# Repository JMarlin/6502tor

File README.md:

# 6502tor

This is the project page for the 6502tor project, a minimal educational computer designed to teach the fundamentals of how a computer actually operates near the lowest levels.

If you received an assembled rev1 board as a holiday gift, it probably looks something like this:

If you're interested in details about how the actual board is designed and built, you should check out the [hardware](hardware/README.md) section.

## Using The Hardware

This computer system is simultaneously incredibly simple while, by the token of complete open-endedness this implies, very complicated. With only a handful of controls, you can get the 6502tor to perform any function that can be done by *any other* computer.

For that reason, most of the system operation is going to be provided by a series of tutorial articles that will be published over time and which can be found below:

### Tutorials:
 - [0000 0001 - Overview and writing to memory](https://youtu.be/rqbeiZjz4c4)
 - [0000 0010 - Memory maps and binary](https://youtu.be/jSdUKUccR5Q)
 - [0000 0011 - Reset vector](https://youtu.be/KTeOp61t6co)
 - [0000 0100 - Executing your first instruction](https://youtu.be/9eZ2-8ygBwk)
 - [0000 0101 - Basic I/O](https://youtu.be/15wBBccO2ps)

### System Overview:

For the purpose of providing a quick reference so that you don't have to read through the articles if you need a reminder, the below chart provides a description of all the basic controls on the board:

1. **USB Port** - Provides power to the system and also, in more advanced uses, serial communication with a host machine

2. **User Register** - Provides 8 bits of output and can be written to at any address between `0x4000` and `0xBFFF`. The top two bits are also attached to the USB chip for more advanced serial I/O purposes:
   - Bit 6: RXD
   - Bit 7: CTS

3. **CPU Reset** - A toggle switch that causes the CPU to do an internal reset when pressed in and allows the CPU to begin executing from the reset vector stored in RAM at `0xFFFC` when released. 
Should be pressed in for at least 3 clock cycles whenever the clock source is changed or in any other scenario where you want the CPU to begin running from its default state.

4. **CLK LED** - Displays the clock signal being fed into the CPU.

5. **Write LED** - Displays whether the system is currently reading or writing data from/to the bus. Probably backwards from what you expect, *there is a write occurring when this LED is **OFF***

6. **Address LEDs** - Display the address that is currently being driven on the address bus, whether that's by the CPU or by the `address switches` (depending on the run/program mode)

7. **Data LEDs** - Display the data that is currently being driven on the data bus, whether that's by the CPU or by the `data switches` (depending on the run/program mode). Note that in run mode, the data bus is only driven during the *high* portion of the clock cycle.

8. **Slow Clock Speed Control** - When the clock source switch is set to 'slow', controls the speed of the slow CPU clock (clockwise is faster).

9. **Step Button** - When the clock source switch is set to 'manual', directly controls the CPU clock. When pressed in, sets the `CLK` signal to low and when not pressed in sets the `CLK` signal to high.
It should be noted that data only appears on the data bus during the high portion of the clock cycle.

10. **Clock Source Switch** - Switches the CPU between three different clock sources/speed ranges:

     - **Full** - Connects the CPU directly to the 5 megahertz crystal oscillator (the metal can in the middle of the board)

     - **Slow** - Connects the CPU to a much slower RC oscillator that can run the CPU between ~0.5 hertz and a few kilohertz depending on how the `Slow Clock Speed Control` is set

     - **Manual** - Connects the clock directly to a debounced pushbutton so that you can manually step through clock cycles as slowly as you would like

11. **Run/Program Switch** - Switches the board between `run` mode, in which the CPU is controlling everything, and the `program` mode in which the CPU is disconnected from the bus and the data switches, address switches, and deposit button can be used to manually place instructions and data into RAM.

12. **Deposit Button** - When the run/program switch is in program mode, depressing this button causes the value set on the data switches to be written to the location specified by the address switches. *This is a toggle button, so make sure to press it twice for each deposit*.

13. **Address Switches** - When the run/program switch is in program mode, the value of these switches is displayed on the address LEDs and the value stored at that location is displayed on the data LEDs. If the deposit switch is pressed, the value on the data switches is written to the address set on these switches.

14. **Data Switches** - When the run/program switch is in program mode, the value on these switches is written to the location set on the address switches. When the run/program switch is in the run mode, the value of the lowest five data switches can be read at addresses from `0x4000` to `0x8FFF`. In this mode, the top three bits connect to the USB chip as follows:

    - Bit 5: TXD
    - Bit 6: RTS
    - Bit 7: DTR 

### Memory Map:
| **Start** | **End** | **Description**                          |
|-----------|---------|------------------------------------------|
| 0x0000    | 0x3FFF  | 32K of RAM                               |
| 0x4000    | 0xBFFF  | Read data switches / Write user register |
| 0xC000    | 0xFFFF  | 32K of RAM                               |

## Reference Material And Resources
 - [6502 CPU datasheet](https://www.westerndesigncenter.com/wdc/documentation/w65c02s.pdf)
 - [6502 CPU instruction reference](https://www.masswerk.at/6502/6502_instruction_set.html)
 - [Online 6502 assembler](https://www.masswerk.at/6502/assembler.html) (for simple manual programming)
 - [cc65 compiler/cc65 assembler](https://github.com/cc65/cc65) (for more involved programming)
 - [RS232 serial communications on wikipedia](https://en.wikipedia.org/wiki/RS-232#Physical_interface)

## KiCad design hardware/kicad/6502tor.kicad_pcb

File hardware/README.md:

# Hardware

This directory contains the schematic and PCB project for the 6502tor hardware. The 6502tor board was designed in KiCAD, an EDA package that is free and open source. If you want to play with the CAD project, you can download KiCAD here:

 - [KiCAD Project Website](https://www.kicad.org/download/)

You can find the project in the `kicad` directory, but if you simply want to view the schematic you can find it in [the PDF in the same directory as this readme](6502tor_schematic.pdf)

## Caveats/Errata

Note that what is included here is the raw version of the project that was used to generate the first revision boards as shipped, and as such both include a handful of errors that are corrected on the shipped hardware with bodge wires:

 - Somehow KiCAD did not indicate to me that I managed to build two separate, unconnected ground nets. This can be fixed by making a connection between the ground pin (pin 10) on the user register IC (the 74574 next to the USB port) and the ground pin (pin 7) of any of the 7400 or 7404 chips in the glue logic section immediately below.

 - The order of the wires connecting the 74244 outputs back to the top three bits of the 74245 data tranceiver is reversed in the design from what it should be. This can be fixed by cutting the three traces that run just above the SMD capacitor located immediately to the left of the right-most 74245 (just above the DIP switches) and then connecting pins 2, 3, and 4 of that IC to pins 12, 14, and 16 of the adjacent 74244.

 - Bizarrely, there's absolutely no connection between the address bit 7 LED and its current-limiting resistor. The fix for this is to connect them.

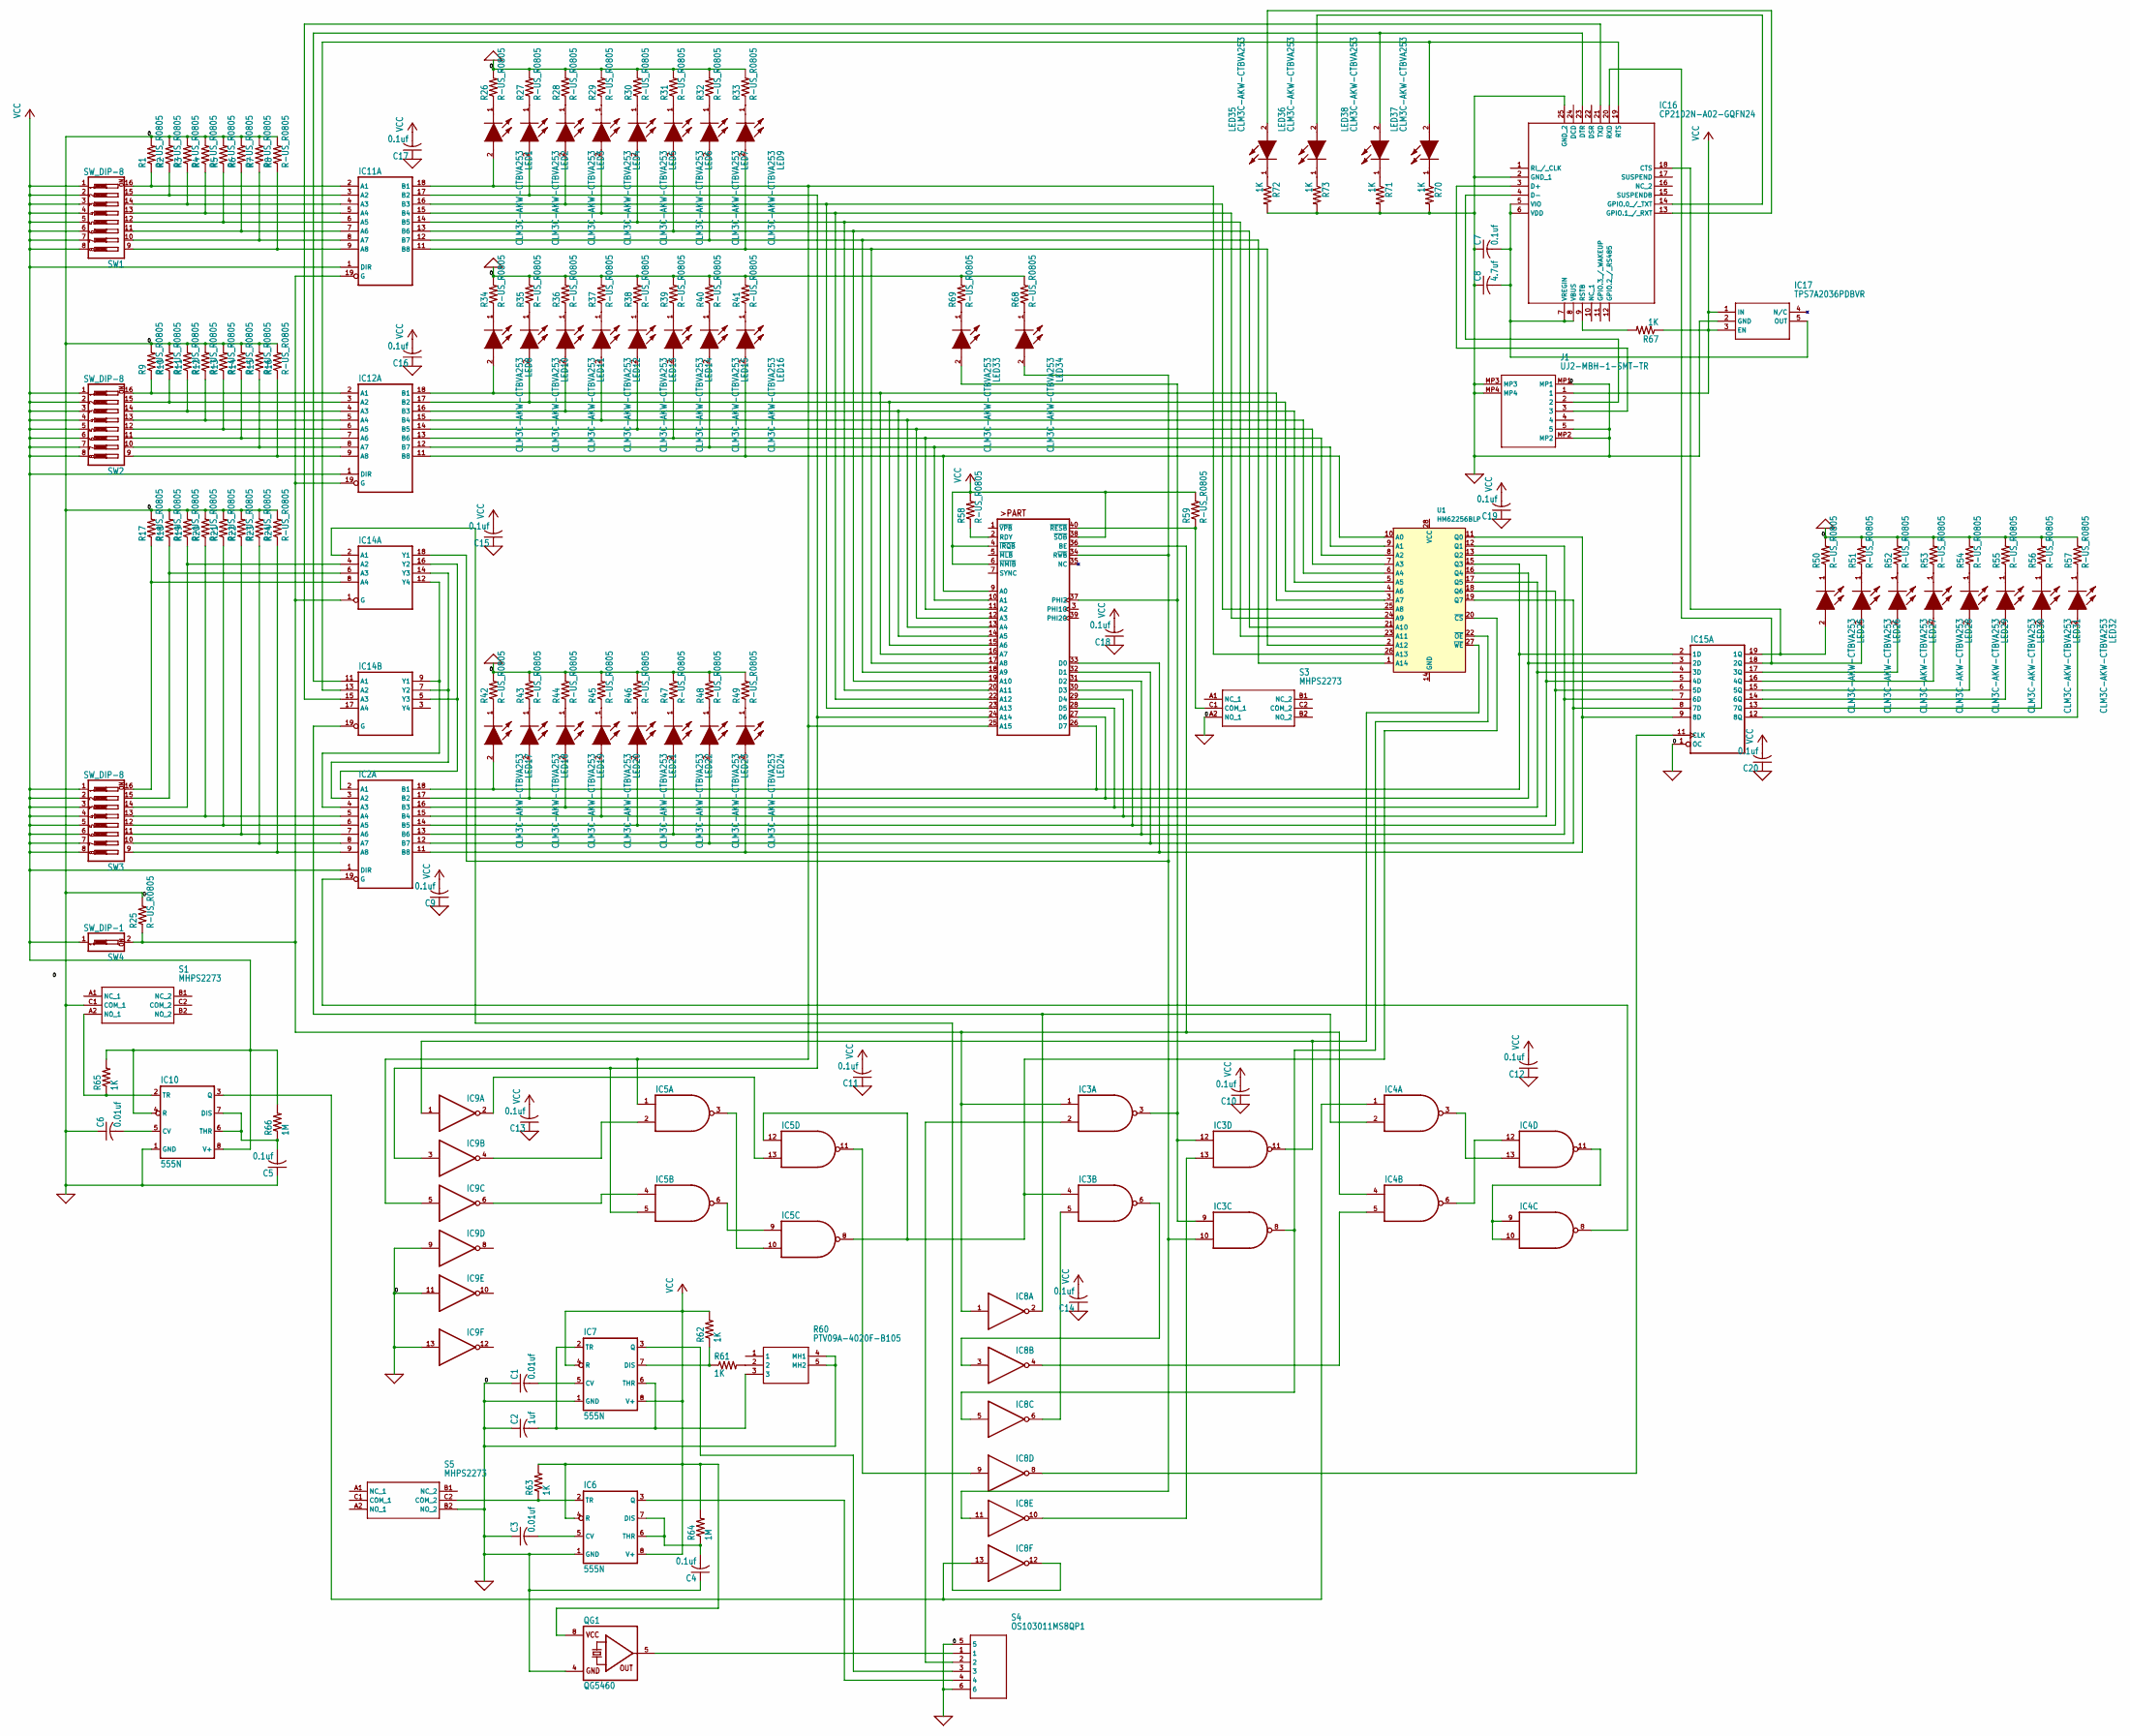
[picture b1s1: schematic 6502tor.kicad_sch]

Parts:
C1, C3, C6: 0.01uf; C1206
C2: 1uf; C1206
C4, C5, C7, C9, C10, C11, C12, C13, C14, C15, C16, C17, C18, C19, C20: 0.1uf; C1206
C8: 4.7uf; C1206
IC1: W65C02SP; DIL40
IC2, IC11, IC12: 74245N; DIL20
IC3, IC4, IC5: 7400N; DIL14
IC6, IC7, IC10: 555N; DIL08
IC8, IC9: 7404N; DIL14
IC14: 74244N; DIL20
IC15: 74574N; DIL20
IC16: CP2102N-A02-GQFN24; QFN50P400X400X80-25N
IC17: TPS7A2036PDBVR; SOT95P280X145-5N
J1: UJ2-MBH-1-SMT-TR; UJ2MBH1SMTTR
LED1, LED2, LED3, LED4, LED5, LED6, LED7, LED8, LED9, LED10, LED11, LED12, LED13, LED14, LED15, LED16, LED17, LED18, LED19, LED20, LED21, LED22, LED23, LED24, LED25, LED26, LED27, LED28, LED29, LED30, LED31, LED32, LED33, LED34, LED35, LED36, LED37, LED38: CLM3C-AKW-CTBVA253; LEDM3020X140N
QG1: QG5460; DIL08S
R1, R2, R3, R4, R5, R6, R7, R8, R9, R10, R11, R12, R13, R14, R15, R16, R17, R18, R19, R20, R21, R22, R23, R24, R25, R26, R27, R28, R29, R30, R31, R32, R33, R34, R35, R36, R37, R38, R39, R40, R41, R42, R43, R44, R45, R46, R47, R48, R49, R50, R51, R52, R53, R54, R55, R56, R57, R58, R59, R68, R69: R-US_R0805; R0805
R60: PTV09A-4020F-B105; PTV09A4020FB103
R61, R62, R63, R65, R67, R70, R71, R72, R73: 1K; R0805
R64, R66: 1M; R0805
S1, S3, S5: MHPS2273
S4: OS103011MS8QP1
SW1, SW2, SW3: SW_DIP-8; EDG-08
SW4: SW_DIP-1; EDG-01
U1: HM62256BLP; DIP-28_W15.24mm

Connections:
0: C1.1, C2.1, C3.1, C4.1, C5.1, C6.1, C7.1, C8.1, C9.1, C10.1, C11.1, C12.1, C13.1, C14.1, C15.1, C16.1, C17.1, C18.1, C19.1, C20.1, IC1.21 (VSS), IC2.10 (GND), IC3.7 (GND), IC4.7 (GND), IC5.7 (GND), IC6.1 (GND), IC7.1 (GND), IC8.7 (GND), IC9.7 (GND), IC9.9 (I), IC9.11 (I), IC9.13 (I), IC10.1 (GND), IC11.10 (GND), IC12.10 (GND), IC14.10 (GND), IC15.1 (OC), IC15.10 (GND), IC16.2 (GND_1), IC16.25 (GND_2), IC17.2 (GND), J1.5, J1.MP1, J1.MP2, J1.MP3, J1.MP4, QG1.4 (GND), R1.2, R2.2, R3.2, R4.2, R5.2, R6.2, R7.2, R8.2, R9.2, R10.2, R11.2, R12.2, R13.2, R14.2, R15.2, R16.2, R17.2, R18.2, R19.2, R20.2, R21.2, R22.2, R23.2, R24.2, R25.2, R26.2, R27.2, R28.2, R29.2, R30.2, R31.2, R32.2, R33.2, R34.2, R35.2, R36.2, R37.2, R38.2, R39.2, R40.2, R41.2, R42.2, R43.2, R44.2, R45.2, R46.2, R47.2, R48.2, R49.2, R50.2, R51.2, R52.2, R53.2, R54.2, R55.2, R56.2, R57.2, R60.4 (MH1), R60.5 (MH2), R68.2, R69.2, R70.2, R71.2, R72.2, R73.2, S1.C1 (COM_1), S3.A2 (NO_1), S4.5, S4.6, S5.B2 (NO_2), U1.14 (GND)
unnamed: C1.2, IC7.5 (CV)
unnamed: C2.2, IC7.2 (TR), IC7.6 (THR), R60.3
unnamed: C3.2, IC6.5 (CV)
unnamed: C4.2, IC6.6 (THR), IC6.7 (DIS), R64.1
unnamed: C5.2, IC10.6 (THR), IC10.7 (DIS), R66.1
unnamed: C6.2, IC10.5 (CV)
unnamed: C7.2, C8.2, IC16.5 (VIO), IC16.6 (VDD), IC16.7 (VREGIN), IC16.8 (VBUS), IC17.5 (OUT)
unnamed: IC1.2 (RDY), R58.1
unnamed: IC1.9 (A0), IC12.11 (B8), LED16.2 (A), U1.10 (A0)
unnamed: IC1.10 (A1), IC12.12 (B7), LED15.2 (A), U1.9 (A1)
unnamed: IC1.11 (A2), IC12.13 (B6), LED14.2 (A), U1.8 (A2)
unnamed: IC1.12 (A3), IC12.14 (B5), LED13.2 (A), U1.7 (A3)
unnamed: IC1.13 (A4), IC12.15 (B4), LED12.2 (A), U1.6 (A4)
unnamed: IC1.14 (A5), IC12.16 (B3), LED11.2 (A), U1.5 (A5)
unnamed: IC1.15 (A6), IC12.17 (B2), LED10.2 (A), U1.4 (A6)
unnamed: IC1.16 (A7), IC12.18 (B1), LED8.2 (A), U1.3 (A7)
unnamed: IC1.17 (A8), IC11.11 (B8), LED9.2 (A), U1.2 (A12)
unnamed: IC1.18 (A9), IC11.12 (B7), LED7.2 (A), U1.1 (A14)
unnamed: IC1.19 (A10), IC11.13 (B6), LED6.2 (A), U1.21 (A10)
unnamed: IC1.20 (A11), IC11.14 (B5), LED5.2 (A), U1.23 (A11)
unnamed: IC1.22 (A12), IC11.15 (B4), LED4.2 (A), U1.24 (A9)
unnamed: IC1.23 (A13), IC11.16 (B3), LED3.2 (A), U1.25 (A8)
unnamed: IC1.24 (A14), IC5.5 (I1), IC9.3 (I), IC11.17 (B2), LED2.2 (A)
unnamed: IC1.25 (A15), IC5.1 (I0), IC9.5 (I), IC11.18 (B1), LED1.2 (A), U1.26 (A13)
unnamed: IC1.26 (D7), IC2.18 (B1), IC15.2 (1D), LED17.2 (A), U1.15 (Q3)
unnamed: IC1.27 (D6), IC2.17 (B2), IC15.3 (2D), LED18.2 (A), U1.16 (Q4)
unnamed: IC1.28 (D5), IC2.16 (B3), IC15.4 (3D), LED19.2 (A), U1.17 (Q5)
unnamed: IC1.29 (D4), IC2.15 (B4), IC15.5 (4D), LED20.2 (A), U1.13 (Q2)
unnamed: IC1.30 (D3), IC2.14 (B5), IC15.6 (5D), LED21.2 (A), U1.18 (Q6)
unnamed: IC1.31 (D2), IC2.13 (B6), IC15.7 (6D), LED22.2 (A), U1.12 (Q1)
unnamed: IC1.32 (D1), IC2.12 (B7), IC15.8 (7D), LED23.2 (A), U1.19 (Q7)
unnamed: IC1.33 (D0), IC2.11 (B8), IC15.9 (8D), LED24.2 (A), U1.11 (Q0)
unnamed: IC1.34 (R~WB), IC3.10 (I1), IC8.11 (I), IC14.18 (Y1), LED34.2 (A)
unnamed: IC1.36 (BE), IC3.1 (I0), IC4.4 (I0), IC8.1 (I), IC11.19 (G), IC12.19 (G), IC14.1 (G), R25.1, SW4.2
unnamed: IC1.37 (PHI2), IC3.3 (O), IC3.9 (I0), IC3.12 (I0), LED33.2 (A)
unnamed: IC1.40 (~RESB), R59.1, S3.C1 (COM_1)
unnamed: IC3.2 (I1), S4.2
unnamed: IC3.4 (I0), IC5.8 (O), IC5.12 (I0), U1.20 (~CS)
unnamed: IC3.5 (I1), IC8.6 (O)
unnamed: IC3.6 (O), IC8.3 (I)
unnamed: IC3.8 (O), IC8.5 (I), U1.22 (~OE)
unnamed: IC3.11 (O), IC9.1 (I), U1.27 (~WE)
unnamed: IC3.13 (I1), IC8.10 (O)
unnamed: IC4.5 (I1), IC8.4 (O)
unnamed: IC2.19 (G), IC4.8 (O)
unnamed: IC4.9 (I0), IC4.10 (I1), IC4.11 (O)
unnamed: IC4.6 (O), IC4.12 (I0)
unnamed: IC4.3 (O), IC4.13 (I1)
unnamed: IC5.2 (I1), IC9.4 (O)
unnamed: IC5.4 (I0), IC9.6 (O)
unnamed: IC5.6 (O), IC5.9 (I0)
unnamed: IC5.3 (O), IC5.10 (I1)
unnamed: IC5.11 (O), IC8.9 (I)
unnamed: IC5.13 (I1), IC9.2 (O)
unnamed: IC6.2 (TR), R63.1, S5.C2 (COM_2)
unnamed: IC6.3 (Q), S4.4
unnamed: IC7.3 (Q), S4.3
unnamed: IC7.7 (DIS), R61.1, R62.1
unnamed: IC10.2 (TR), R65.1, S1.A2 (NO_1)
unnamed: IC4.1 (I0), IC8.13 (I), IC10.3 (Q)
unnamed: IC11.2 (A1), R1.1, SW1.16
unnamed: IC11.3 (A2), R2.1, SW1.15
unnamed: IC11.4 (A3), R3.1, SW1.14
unnamed: IC11.5 (A4), R4.1, SW1.13
unnamed: IC11.6 (A5), R5.1, SW1.12
unnamed: IC11.7 (A6), R6.1, SW1.11
unnamed: IC11.8 (A7), R7.1, SW1.10
unnamed: IC11.9 (A8), R8.1, SW1.9
unnamed: IC12.2 (A1), R9.1, SW2.16
unnamed: IC12.3 (A2), R10.1, SW2.15
unnamed: IC12.4 (A3), R11.1, SW2.14
unnamed: IC12.5 (A4), R12.1, SW2.13
unnamed: IC12.6 (A5), R13.1, SW2.12
unnamed: IC12.7 (A6), R14.1, SW2.11
unnamed: IC12.8 (A7), R15.1, SW2.10
unnamed: IC12.9 (A8), R16.1, SW2.9
unnamed: IC8.12 (O), IC14.2 (A1)
unnamed: IC14.4 (A2), R19.1, SW3.14
unnamed: IC14.6 (A3), R18.1, SW3.15
unnamed: IC14.8 (A4), R17.1, SW3.16
unnamed: IC14.11 (A1), IC16.23 (DTR), LED38.2 (A)
unnamed: IC2.4 (A3), IC14.9 (Y1), IC14.12 (Y4)
unnamed: IC14.13 (A2), IC16.19 (RTS), LED37.2 (A)
unnamed: IC2.3 (A2), IC14.7 (Y2), IC14.14 (Y3)
unnamed: IC14.15 (A3), IC16.21 (TXD)
unnamed: IC2.2 (A1), IC14.5 (Y3), IC14.16 (Y2)
unnamed: IC4.2 (I1), IC8.2 (O), IC14.19 (G)
unnamed: IC8.8 (O), IC15.11 (CLK)
unnamed: IC15.12 (8Q), LED32.2 (A)
unnamed: IC15.13 (7Q), LED31.2 (A)
unnamed: IC15.14 (6Q), LED30.2 (A)
unnamed: IC15.15 (5Q), LED29.2 (A)
unnamed: IC15.16 (4Q), LED28.2 (A)
unnamed: IC15.17 (3Q), LED27.2 (A)
unnamed: IC15.18 (2Q), IC16.20 (RXD), LED26.2 (A)
unnamed: IC15.19 (1Q), IC16.18 (CTS), LED25.2 (A)
unnamed: IC16.3 (D+), J1.3
unnamed: IC16.4 (D-), J1.2
unnamed: IC16.9 (RSTB), R67.2
unnamed: IC16.13 (GPIO.1_/_RXT), LED35.2 (A)
unnamed: IC16.14 (GPIO.0_/_TXT), LED36.2 (A)
unnamed: LED1.1 (K), R26.1
unnamed: LED2.1 (K), R27.1
unnamed: LED3.1 (K), R28.1
unnamed: LED4.1 (K), R29.1
unnamed: LED5.1 (K), R30.1
unnamed: LED6.1 (K), R31.1
unnamed: LED7.1 (K), R32.1
unnamed: LED8.1 (K), R34.1
unnamed: LED9.1 (K), R33.1
unnamed: LED10.1 (K), R35.1
unnamed: LED11.1 (K), R36.1
unnamed: LED12.1 (K), R37.1
unnamed: LED13.1 (K), R38.1
unnamed: LED14.1 (K), R39.1
unnamed: LED15.1 (K), R40.1
unnamed: LED16.1 (K), R41.1
unnamed: LED17.1 (K), R42.1
unnamed: LED18.1 (K), R43.1
unnamed: LED19.1 (K), R44.1
unnamed: LED20.1 (K), R45.1
unnamed: LED21.1 (K), R46.1
unnamed: LED22.1 (K), R47.1
unnamed: LED23.1 (K), R48.1
unnamed: LED24.1 (K), R49.1
unnamed: LED25.1 (K), R50.1
unnamed: LED26.1 (K), R51.1
unnamed: LED27.1 (K), R52.1
unnamed: LED28.1 (K), R53.1
unnamed: LED29.1 (K), R54.1
unnamed: LED30.1 (K), R55.1
unnamed: LED31.1 (K), R56.1
unnamed: LED32.1 (K), R57.1
unnamed: LED33.1 (K), R69.1
unnamed: LED34.1 (K), R68.1
unnamed: LED35.1 (K), R72.1
unnamed: LED36.1 (K), R73.1
unnamed: LED37.1 (K), R70.1
unnamed: LED38.1 (K), R71.1
unnamed: QG1.5 (OUT), S4.1
unnamed: IC2.5 (A4), R20.1, SW3.13
unnamed: IC2.6 (A5), R21.1, SW3.12
unnamed: IC2.7 (A6), R22.1, SW3.11
unnamed: IC2.8 (A7), R23.1, SW3.10
unnamed: IC2.9 (A8), R24.1, SW3.9
unnamed: R60.2, R61.2
VCC: C9.2, C10.2, C11.2, C12.2, C13.2, C14.2, C15.2, C16.2, C17.2, C18.2, C19.2, C20.2, IC1.4 (~IRQB), IC1.6 (~NMIB), IC1.8 (VDD), IC1.38 (~SOB), IC2.1 (DIR), IC2.20 (VCC), IC3.14 (VCC), IC4.14 (VCC), IC5.14 (VCC), IC6.4 (R), IC6.8 (V+), IC7.4 (R), IC7.8 (V+), IC8.14 (VCC), IC9.14 (VCC), IC10.4 (R), IC10.8 (V+), IC11.1 (DIR), IC11.20 (VCC), IC12.1 (DIR), IC12.20 (VCC), IC14.20 (VCC), IC15.20 (VCC), IC17.1 (IN), IC17.3 (EN), J1.1, QG1.8 (VCC), R58.2, R59.2, R62.2, R63.2, R64.2, R65.2, R66.2, R67.1, SW1.1, SW1.2, SW1.3, SW1.4, SW1.5, SW1.6, SW1.7, SW1.8, SW2.1, SW2.2, SW2.3, SW2.4, SW2.5, SW2.6, SW2.7, SW2.8, SW3.1, SW3.2, SW3.3, SW3.4, SW3.5, SW3.6, SW3.7, SW3.8, SW4.1, U1.28 (VCC)

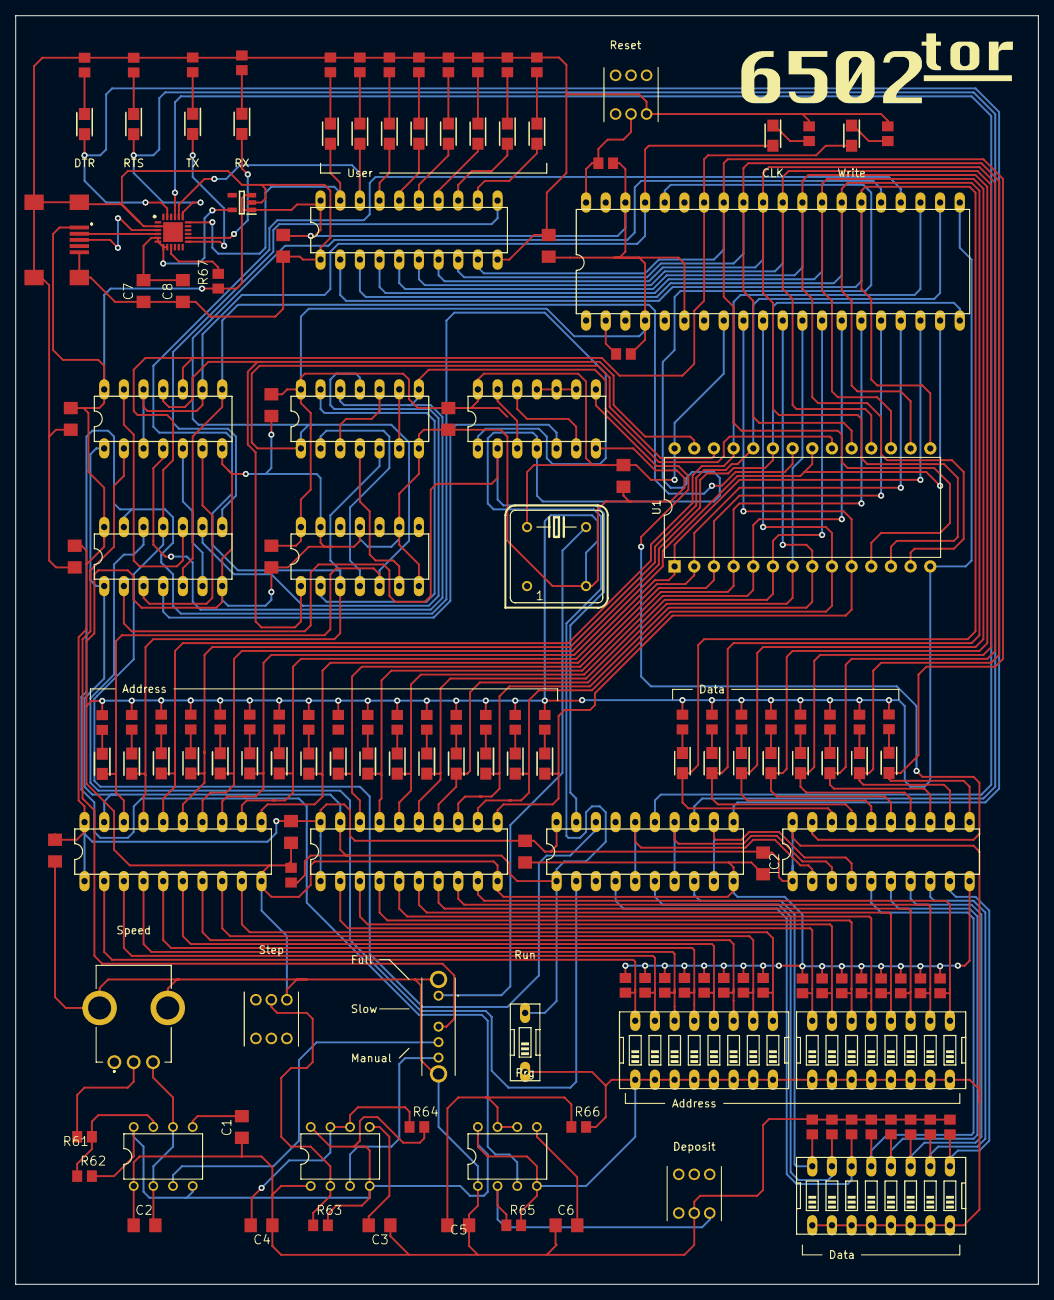
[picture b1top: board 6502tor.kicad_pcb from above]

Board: 2 copper layers, 132.1 x 163.8 mm, 158 parts (0 on the bottom side), 148 nets.

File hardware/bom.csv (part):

"Source:","/Users/josephmarlin/Documents/KiCad/6.0/projects/6502tor/6502tor.kicad_sch"
"Date:","Wednesday, December 07, 2022 at 05:16:50 PM"
"Tool:","Eeschema (6.0.9-0)"
"Generator:","/Applications/KiCad/KiCad.app/Contents/SharedSupport/plugins/bom_csv_grouped_by_value.py"
"Component Count:","158"

"Individual Components:"

"Item","Qty","Reference(s)","Value","LibPart","Footprint","Datasheet"
"","","C1","0.01uf","6502tor-eagle-import:C-USC1206","6502tor:C1206",""
"","","C2","1uf","6502tor-eagle-import:C-USC1206","6502tor:C1206",""
"","","C3","0.01uf","6502tor-eagle-import:C-USC1206","6502tor:C1206",""
"","","C4","0.1uf","6502tor-eagle-import:C-USC1206","6502tor:C1206",""
"","","C5","0.1uf","6502tor-eagle-import:C-USC1206","6502tor:C1206",""
"","","C6","0.01uf","6502tor-eagle-import:C-USC1206","6502tor:C1206",""
"","","C7","0.1uf","6502tor-eagle-import:C-USC1206","6502tor:C1206",""
"","","C8","4.7uf","6502tor-eagle-import:C-USC1206","6502tor:C1206",""
"","","C9","0.1uf","6502tor-eagle-import:C-USC1206","6502tor:C1206",""
"","","C10","0.1uf","6502tor-eagle-import:C-USC1206","6502tor:C1206",""
"","","C11","0.1uf","6502tor-eagle-import:C-USC1206","6502tor:C1206",""
"","","C12","0.1uf","6502tor-eagle-import:C-USC1206","6502tor:C1206",""
"","","C13","0.1uf","6502tor-eagle-import:C-USC1206","6502tor:C1206",""
"","","C14","0.1uf","6502tor-eagle-import:C-USC1206","6502tor:C1206",""
"","","C15","0.1uf","6502tor-eagle-import:C-USC1206","6502tor:C1206",""
"","","C16","0.1uf","6502tor-eagle-import:C-USC1206","6502tor:C1206",""
"","","C17","0.1uf","6502tor-eagle-import:C-USC1206","6502tor:C1206",""
"","","C18","0.1uf","6502tor-eagle-import:C-USC1206","6502tor:C1206",""
"","","C19","0.1uf","6502tor-eagle-import:C-USC1206","6502tor:C1206",""
"","","C20","0.1uf","6502tor-eagle-import:C-USC1206","6502tor:C1206",""
"","","IC1","W65C02SP","6502tor-eagle-import:W65C02SP","6502tor:DIL40",""
"","","IC2","74245N","6502tor-eagle-import:74245N","6502tor:DIL20",""
"","","IC3","7400N","6502tor-eagle-import:7400N","6502tor:DIL14",""
"","","IC4","7400N","6502tor-eagle-import:7400N","6502tor:DIL14",""
"","","IC5","7400N","6502tor-eagle-import:7400N","6502tor:DIL14",""
"","","IC6","555N","6502tor-eagle-import:555N","6502tor:DIL08",""
"","","IC7","555N","6502tor-eagle-import:555N","6502tor:DIL08",""
"","","IC8","7404N","6502tor-eagle-import:7404N","6502tor:DIL14",""
"","","IC9","7404N","6502tor-eagle-import:7404N","6502tor:DIL14",""
"","","IC10","555N","6502tor-eagle-import:555N","6502tor:DIL08",""
"","","IC11","74245N","6502tor-eagle-import:74245N","6502tor:DIL20",""
"","","IC12","74245N","6502tor-eagle-import:74245N","6502tor:DIL20",""
"","","IC14","74244N","6502tor-eagle-import:74244N","6502tor:DIL20",""
"","","IC15","74574N","6502tor-eagle-import:74574N","6502tor:DIL20",""
"","","IC16","CP2102N-A02-GQFN24","6502tor-eagle-import:CP2102N-A02-GQFN24","6502tor:QFN50P400X400X80-25N",""
"","","IC17","TPS7A2036PDBVR","6502tor-eagle-import:TPS7A2036PDBVR","6502tor:SOT95P280X145-5N",""
"","","J1","UJ2-MBH-1-SMT-TR","6502tor-eagle-import:UJ2-MBH-1-SMT-TR","6502tor:UJ2MBH1SMTTR",""
"","","LED1","CLM3C-AKW-CTBVA253","6502tor-eagle-import:CLM3C-AKW-CTBVA253","6502tor:LEDM3020X140N",""
"","","LED2","CLM3C-AKW-CTBVA253","6502tor-eagle-import:CLM3C-AKW-CTBVA253","6502tor:LEDM3020X140N",""
"","","LED3","CLM3C-AKW-CTBVA253","6502tor-eagle-import:CLM3C-AKW-CTBVA253","6502tor:LEDM3020X140N",""
"","","LED4","CLM3C-AKW-CTBVA253","6502tor-eagle-import:CLM3C-AKW-CTBVA253","6502tor:LEDM3020X140N",""
"","","LED5","CLM3C-AKW-CTBVA253","6502tor-eagle-import:CLM3C-AKW-CTBVA253","6502tor:LEDM3020X140N",""
"","","LED6","CLM3C-AKW-CTBVA253","6502tor-eagle-import:CLM3C-AKW-CTBVA253","6502tor:LEDM3020X140N",""
"","","LED7","CLM3C-AKW-CTBVA253","6502tor-eagle-import:CLM3C-AKW-CTBVA253","6502tor:LEDM3020X140N",""
"","","LED8","CLM3C-AKW-CTBVA253","6502tor-eagle-import:CLM3C-AKW-CTBVA253","6502tor:LEDM3020X140N",""
"","","LED9","CLM3C-AKW-CTBVA253","6502tor-eagle-import:CLM3C-AKW-CTBVA253","6502tor:LEDM3020X140N",""
"","","LED10","CLM3C-AKW-CTBVA253","6502tor-eagle-import:CLM3C-AKW-CTBVA253","6502tor:LEDM3020X140N",""
"","","LED11","CLM3C-AKW-CTBVA253","6502tor-eagle-import:CLM3C-AKW-CTBVA253","6502tor:LEDM3020X140N",""
"","","LED12","CLM3C-AKW-CTBVA253","6502tor-eagle-import:CLM3C-AKW-CTBVA253","6502tor:LEDM3020X140N",""
"","","LED13","CLM3C-AKW-CTBVA253","6502tor-eagle-import:CLM3C-AKW-CTBVA253","6502tor:LEDM3020X140N",""
"","","LED14","CLM3C-AKW-CTBVA253","6502tor-eagle-import:CLM3C-AKW-CTBVA253","6502tor:LEDM3020X140N",""
"","","LED15","CLM3C-AKW-CTBVA253","6502tor-eagle-import:CLM3C-AKW-CTBVA253","6502tor:LEDM3020X140N",""
"","","LED16","CLM3C-AKW-CTBVA253","6502tor-eagle-import:CLM3C-AKW-CTBVA253","6502tor:LEDM3020X140N",""
"","","LED17","CLM3C-AKW-CTBVA253","6502tor-eagle-import:CLM3C-AKW-CTBVA253","6502tor:LEDM3020X140N",""
"","","LED18","CLM3C-AKW-CTBVA253","6502tor-eagle-import:CLM3C-AKW-CTBVA253","6502tor:LEDM3020X140N",""
"","","LED19","CLM3C-AKW-CTBVA253","6502tor-eagle-import:CLM3C-AKW-CTBVA253","6502tor:LEDM3020X140N",""
"","","LED20","CLM3C-AKW-CTBVA253","6502tor-eagle-import:CLM3C-AKW-CTBVA253","6502tor:LEDM3020X140N",""
"","","LED21","CLM3C-AKW-CTBVA253","6502tor-eagle-import:CLM3C-AKW-CTBVA253","6502tor:LEDM3020X140N",""
"","","LED22","CLM3C-AKW-CTBVA253","6502tor-eagle-import:CLM3C-AKW-CTBVA253","6502tor:LEDM3020X140N",""
"","","LED23","CLM3C-AKW-CTBVA253","6502tor-eagle-import:CLM3C-AKW-CTBVA253","6502tor:LEDM3020X140N",""
"","","LED24","CLM3C-AKW-CTBVA253","6502tor-eagle-import:CLM3C-AKW-CTBVA253","6502tor:LEDM3020X140N",""
"","","LED25","CLM3C-AKW-CTBVA253","6502tor-eagle-import:CLM3C-AKW-CTBVA253","6502tor:LEDM3020X140N",""
"","","LED26","CLM3C-AKW-CTBVA253","6502tor-eagle-import:CLM3C-AKW-CTBVA253","6502tor:LEDM3020X140N",""
"","","LED27","CLM3C-AKW-CTBVA253","6502tor-eagle-import:CLM3C-AKW-CTBVA253","6502tor:LEDM3020X140N",""
"","","LED28","CLM3C-AKW-CTBVA253","6502tor-eagle-import:CLM3C-AKW-CTBVA253","6502tor:LEDM3020X140N",""
"","","LED29","CLM3C-AKW-CTBVA253","6502tor-eagle-import:CLM3C-AKW-CTBVA253","6502tor:LEDM3020X140N",""
"","","LED30","CLM3C-AKW-CTBVA253","6502tor-eagle-import:CLM3C-AKW-CTBVA253","6502tor:LEDM3020X140N",""
"","","LED31","CLM3C-AKW-CTBVA253","6502tor-eagle-import:CLM3C-AKW-CTBVA253","6502tor:LEDM3020X140N",""
"","","LED32","CLM3C-AKW-CTBVA253","6502tor-eagle-import:CLM3C-AKW-CTBVA253","6502tor:LEDM3020X140N",""
"","","LED33","CLM3C-AKW-CTBVA253","6502tor-eagle-import:CLM3C-AKW-CTBVA253","6502tor:LEDM3020X140N",""
"","","LED34","CLM3C-AKW-CTBVA253","6502tor-eagle-import:CLM3C-AKW-CTBVA253","6502tor:LEDM3020X140N",""
"","","LED35","CLM3C-AKW-CTBVA253","6502tor-eagle-import:CLM3C-AKW-CTBVA253","6502tor:LEDM3020X140N",""
"","","LED36","CLM3C-AKW-CTBVA253","6502tor-eagle-import:CLM3C-AKW-CTBVA253","6502tor:LEDM3020X140N",""
"","","LED37","CLM3C-AKW-CTBVA253","6502tor-eagle-import:CLM3C-AKW-CTBVA253","6502tor:LEDM3020X140N",""
"","","LED38","CLM3C-AKW-CTBVA253","6502tor-eagle-import:CLM3C-AKW-CTBVA253","6502tor:LEDM3020X140N",""
"","","QG1","QG5460","6502tor-eagle-import:QG5460","6502tor:DIL08S",""
"","","R1","R-US_R0805","6502tor-eagle-import:R-US_R0805","6502tor:R0805",""
"","","R2","R-US_R0805","6502tor-eagle-import:R-US_R0805","6502tor:R0805",""
"","","R3","R-US_R0805","6502tor-eagle-import:R-US_R0805","6502tor:R0805",""
"","","R4","R-US_R0805","6502tor-eagle-import:R-US_R0805","6502tor:R0805",""
"","","R5","R-US_R0805","6502tor-eagle-import:R-US_R0805","6502tor:R0805",""
"","","R6","R-US_R0805","6502tor-eagle-import:R-US_R0805","6502tor:R0805",""
"","","R7","R-US_R0805","6502tor-eagle-import:R-US_R0805","6502tor:R0805",""
"","","R8","R-US_R0805","6502tor-eagle-import:R-US_R0805","6502tor:R0805",""
"","","R9","R-US_R0805","6502tor-eagle-import:R-US_R0805","6502tor:R0805",""
"","","R10","R-US_R0805","6502tor-eagle-import:R-US_R0805","6502tor:R0805",""
"","","R11","R-US_R0805","6502tor-eagle-import:R-US_R0805","6502tor:R0805",""
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
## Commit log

2022-12-17 Initial main page and hardware section
2022-12-21 Add tutor_butor source, remove .DS_Store
2022-12-21 Restore swapped DTR and RTS in tutor butor
2023-01-28 Update butor files, add first tutorial link
2023-02-17 Add tutorial #2
2023-02-17 Fix video link
2023-02-20 Add third tutorial link
2023-02-26 Add tutorial video #4
2023-03-14 Add tutorial #5 link
